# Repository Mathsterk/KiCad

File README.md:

# KiCad
**Random projects**

remember to unzip submodules (OPL)
remember to add proper library path (../../Library)
remember something else as well
remember to use relative paths

## Projects
  this is where you put projects

## Library

  this is where libraries go, both component and footprints

## Tools
  where random scripts and stuff lives

## Board assemblies
  this is where 3d-ifyed stuff can live, preferrably within ./\<project name>/<3d-files>

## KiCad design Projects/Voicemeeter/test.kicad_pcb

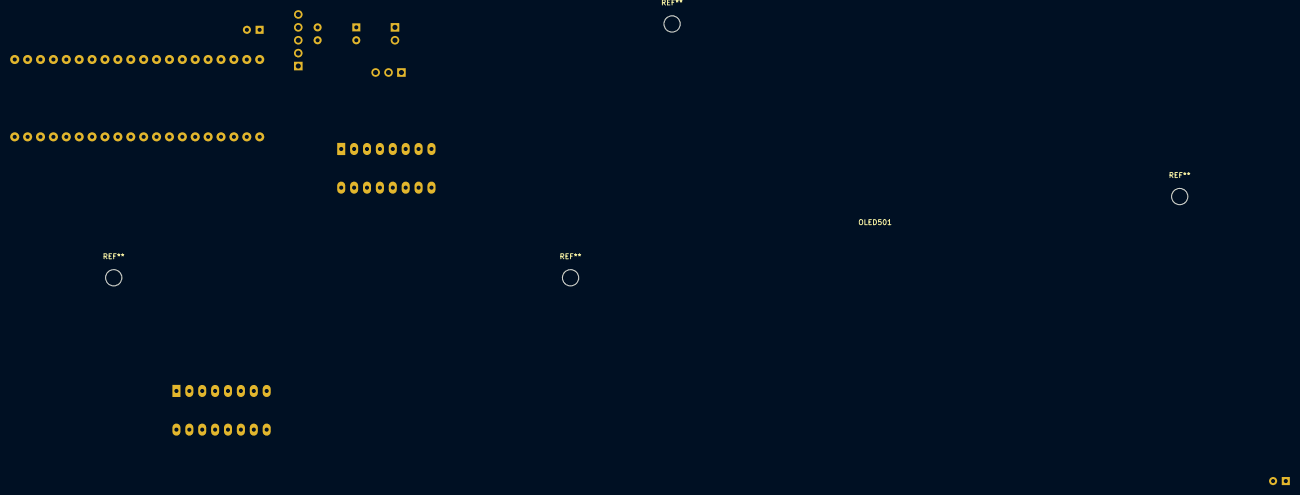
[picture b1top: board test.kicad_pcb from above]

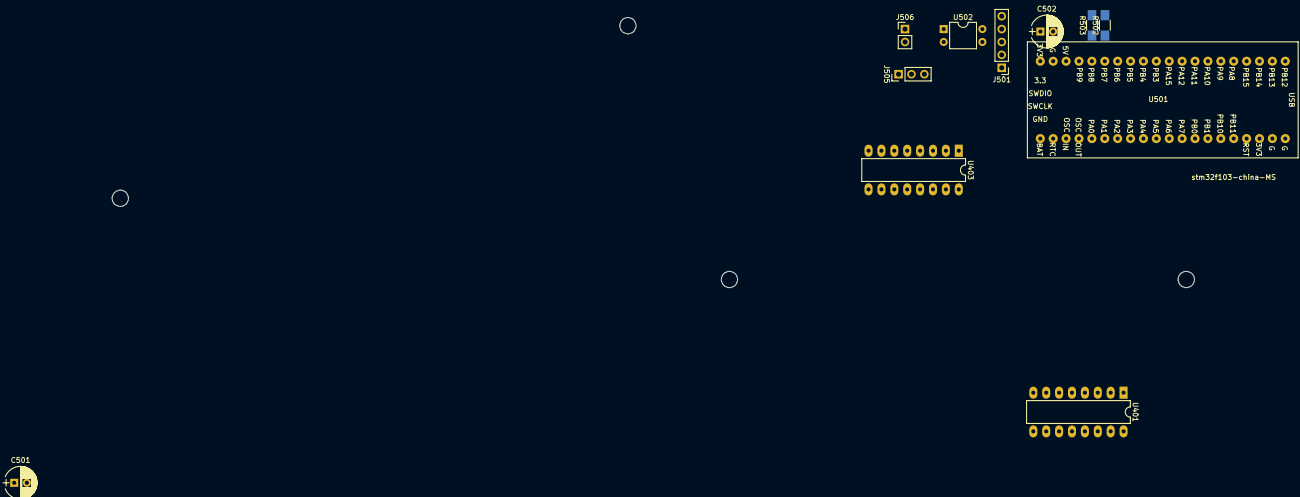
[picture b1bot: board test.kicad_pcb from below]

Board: 2 copper layers, 12 parts (11 on the bottom side), 11 nets, no tracks yet.

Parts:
C501, C502: 220uF; CP_Radial_D6.3mm_P2.50mm
J501: SPARE; Pin_Header_Straight_1x05_Pitch2.54mm
J505: MIDI OUT; Pin_Header_Straight_1x03_Pitch2.54mm
J506: MIDI IN; Pin_Header_Straight_1x02_Pitch2.54mm
OLED501: 1.5; OLED
R502, R503: 10K; R_1206_HandSoldering
U401, U403: 74HC4051; DIP-16_W7.62mm_LongPads
U501: stm32f103-china-MS; stm32f103c8t6-module-china-MS
U502: PC817; DIP-4_W7.62mm

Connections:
+3V3: C502.1, J501.1, U401.6, U401.16, U403.6, U403.16, U501.20, U501.38
+5V: C501.1, J501.3, U501.18
/Mux/M1: U401.11, U403.11
/Mux/M2: U401.10, U403.10
/Mux/M3: U401.9, U403.9
GND: C501.2, C502.2, J501.2, J505.2, U401.8, U403.8, U501.19, U501.39, U501.40, U502.3
unnamed: J506.1, U502.1
unnamed: J506.2, U502.2
unnamed: R502.1, U501.15
unnamed: R503.1, U501.16
unnamed: U501.27, U502.4

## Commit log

2018-05-08 added myelin-kicad-libraries
2018-05-08 added own stuff
2018-05-08 ingoring extracted seeed opl
2018-05-08 eh, weirdness
2018-05-08 more weirdness
2018-05-08 added some stuff
2018-05-08 added digikey library
2018-05-08 more stuff
2018-05-08 added voicemeeter project
2018-05-08 added placeholder in directories
2018-05-08 added myelin's .pretty
2018-05-08 readme again
2018-05-08 fix libs
2018-05-08 fixed a header
2018-05-09 library stuff
2018-05-09 blah
2018-05-09 urgh
2018-05-09 taking a break
2018-05-09 readme, readyou
2018-05-09 enter?
2018-05-09 another placeholder
2018-05-09 asdasdasdasd
2018-05-09 i knew i fucked up something
2018-05-09 added schematic
2018-05-09 colors plz
2018-05-09 stuff
2018-05-09 found it!
2018-05-09 Zzzzz
2018-05-10 morning
2018-05-10 switching to desktop
2018-05-11 ASDASD
2018-05-11 dvcvcv
2018-05-11 why did a lock file sneak in? <.<
2018-05-11 considering stuff
2018-05-14 need to do stuff elsewhere
2018-05-14 uuuuuugh
2018-05-14 boop
2018-05-14 before something dies
2018-05-15 moar leds, more powah
2018-05-15 moar pdf
2018-05-15 in case of emergency
2018-05-15 added images
2018-05-15 wrong dir
2018-05-15 zzzz
2018-05-16 vada
2018-05-16 starting to get bored
2018-05-22 before it's too late
2018-05-22 something something
2018-05-22 well, traces are routed, noone remains
2018-05-22 bleh
    didn't need placeholder
2018-05-23 sooon (tm)
2018-05-23 made a pdf of copper layers
2018-05-23 finito
2018-05-24 asdf
2018-05-24 das boot
2018-05-24 3d3d3d3d3d
2018-05-24 ... wrong size
2018-05-24 deleted some test files
2018-05-24 lolololololol
2018-05-24 qqwwwwww
2018-05-24 idfk
2018-05-24 cleaning up the mess
2018-05-28 1 step
2018-05-28 yay, stuff
2018-05-28 testing
2018-05-28 spring cleaning
2018-05-28 fixing 3d path...
2018-05-28 fixed some paths
2018-05-28 rararara
2018-05-28 removing more crap
2018-05-28 argghhhh
2018-05-28 finally!
2018-05-28 moar holes!
2018-05-28 it's holey
2018-05-28 ok..
